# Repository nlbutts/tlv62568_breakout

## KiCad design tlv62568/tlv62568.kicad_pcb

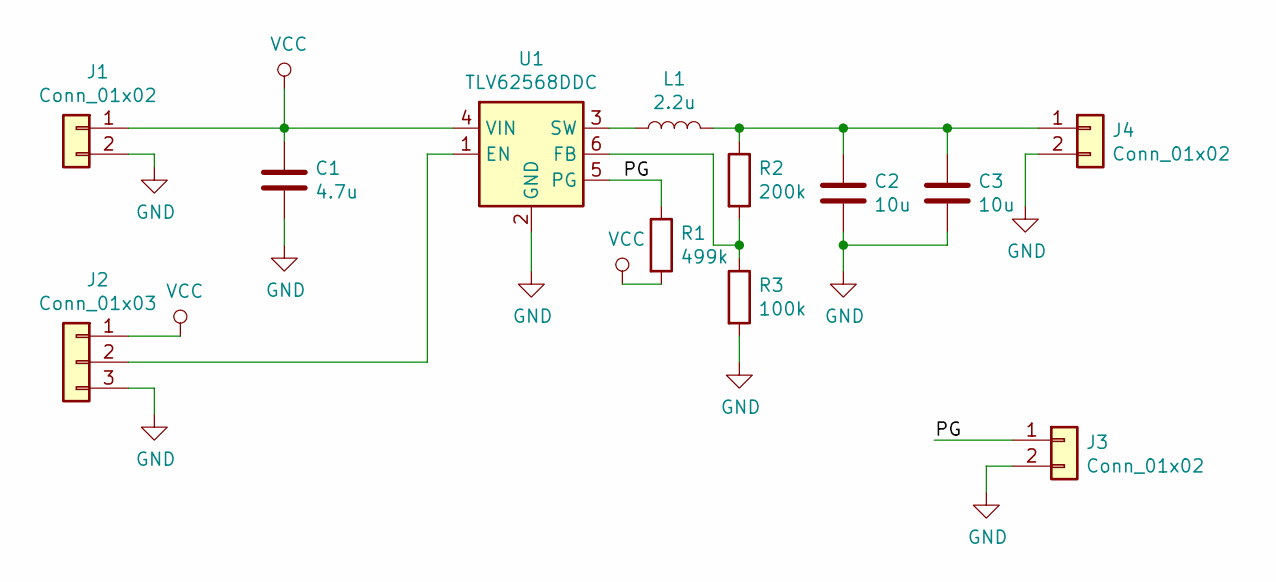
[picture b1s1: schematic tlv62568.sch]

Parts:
C1: 4.7u; C_0603_1608Metric_Pad1.05x0.95mm_HandSolder
C2, C3: 10u; C_0603_1608Metric_Pad1.05x0.95mm_HandSolder
J1, J3, J4: Conn_01x02; PinHeader_1x02_P2.54mm_Vertical
J2: Conn_01x03; PinHeader_1x03_P2.54mm_Vertical
L1: 2.2u; L_2816_7142Metric_Pad3.20x4.45mm_HandSolder
R1: 499k; R_0603_1608Metric_Pad1.05x0.95mm_HandSolder
R2: 200k; R_0603_1608Metric_Pad1.05x0.95mm_HandSolder
R3: 100k; R_0603_1608Metric_Pad1.05x0.95mm_HandSolder
U1: TLV62568DDC; SOT-23-6

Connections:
/PG: J3.1, R1.1, U1.5 (PG)
GND: C1.2, C2.2, C3.2, J1.2, J2.3, J3.2, J4.2, R3.2, U1.2 (GND)
unnamed: C2.1, C3.1, J4.1, L1.2, R2.1
unnamed: J2.2, U1.1 (EN)
unnamed: L1.1, U1.3 (SW)
unnamed: R2.2, R3.1, U1.6 (FB)
VCC: C1.1, J1.1, J2.1, R1.2, U1.4 (VIN)

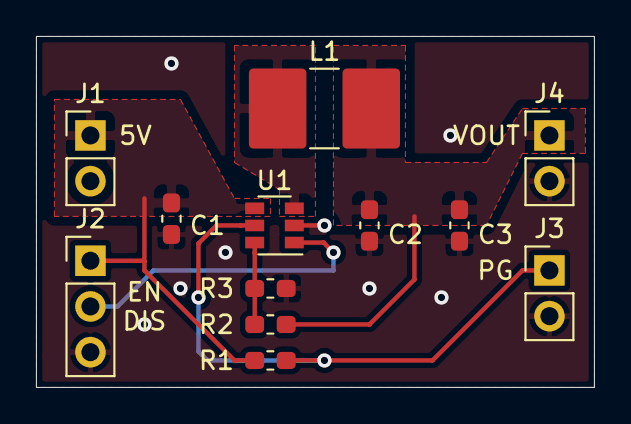
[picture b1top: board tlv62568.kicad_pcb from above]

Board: 2 copper layers, 31.0 x 19.5 mm, 12 parts (0 on the bottom side), 7 nets.

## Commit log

2020-04-30 Initial checkin

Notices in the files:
tlv62568/tlv62568.kicad_pcb:
Copyright 2020
